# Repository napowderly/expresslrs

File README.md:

# expresslrs

Wooohooo a new package!

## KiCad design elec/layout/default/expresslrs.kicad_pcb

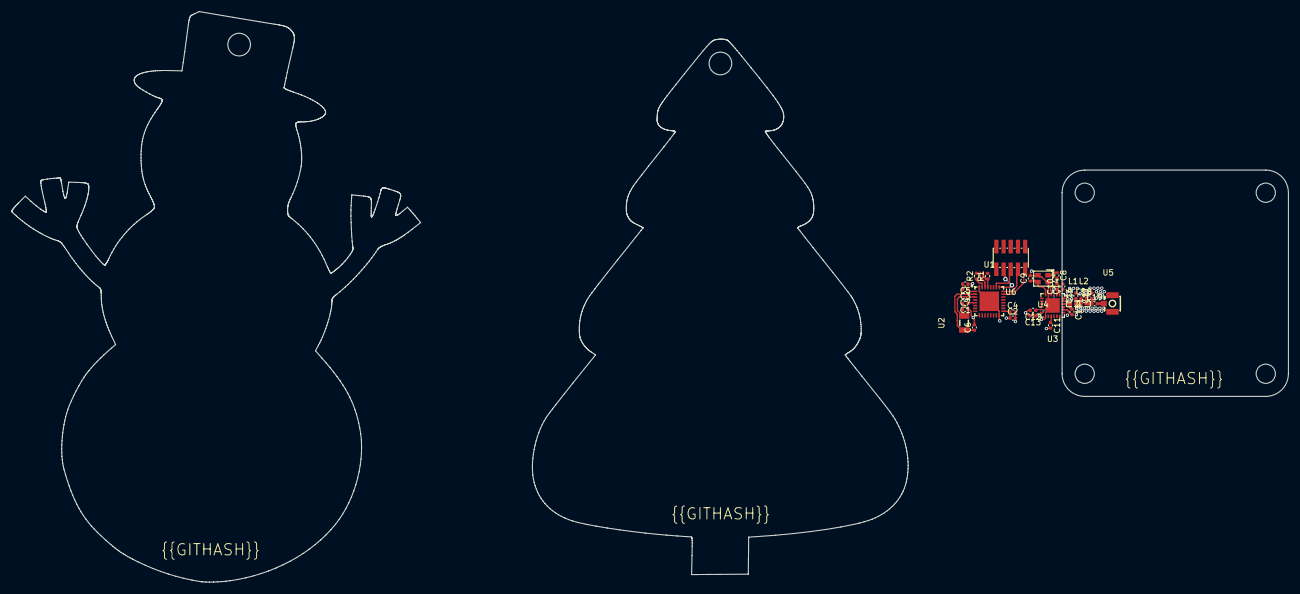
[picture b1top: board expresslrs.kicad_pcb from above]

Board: 2 copper layers, 29 parts (0 on the bottom side), 28 nets.

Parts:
C1: 10V 4.7uF X5R ±20% 0402 Multilayer Ceramic Capaci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; C0402
C2, C4, C11, C12: Multilayer Ceramic Capacitors MLCC - SMD/SMT 100n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; C0402
C3: Multilayer Ceramic Capacitors MLCC - SMD/SMT 1uF 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; C0402
C5, C13, C14: 50V 10nF X7R ±10% 0402 Multilayer Ceramic Capacit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; C0402
C6, C7: 50V 13pF C0G ±2% 0402 Multilayer Ceramic Capacito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; C0402
C8, C9: Multilayer Ceramic Capacitors MLCC - SMD/SMT 10pF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; C0402
C10: 10V 470nF X5R ±10% 0402 Multilayer Ceramic Capaci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; C0402
C15, C18: 50V 1pF C0G 0402 Multilayer Ceramic Capacitors ML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; C0402
C16, C17: Multilayer Ceramic Capacitors MLCC - SMD/SMT 1.2p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; C0402
C19: 50V 100pF C0G ±5% 0402 Multilayer Ceramic Capacit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; C0402
L1, L2: L0402
R1: Chip Resistor - Surface Mount 330Ohms ±5% 1/16W 0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; R0402
R2: Chip Resistor - Surface Mount 10KOhms ±5% 1/16W 0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; R0402
U1: UFQFPN-32_L5.0-W5.0-P0.50-TL-EP3.5
U2: FC-135R_L3.2-W1.5
U3: QFN-24_L4.0-W4.0-P0.50-BL-EP2.6
U4: OSC-SMD_4P-L2.0-W1.6-BL
U5: IPEX-SMD_BWIPX-1-001E
U6: HDR-SMD_10P-P1.27-V-M-R2-C5-LS5.3

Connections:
cs: U1.10, U3.19
gnd: C1.2, C2.2, C3.2, C4.2, C5.2, C6.2, C7.2, C8.2, C9.2, C10.2, C11.2, C12.2, C13.2, C14.2, C15.2, C16.2, C17.2, R2.2, U1.16, U1.32, U1.33, U3.5, U3.13, U3.20, U3.21, U3.23, U3.24, U3.25, U5.2, U5.3, U6.3, U6.5, U6.9
gnd-2: U4.2, U4.4
gnd-3: C19.2, U5.1
io: U1.18, U3.10
io-1: U1.21, U3.7
io-2: U1.27, U3.3
io-3: C15.1, L1.1, U3.22
miso: U1.12, U3.16
mosi: U1.13, U3.17
pc14_osc32_in: C6.1, U1.2, U2.1
pc15_osc32_out: C7.1, U1.3, U2.2
ph3_boot0: R2.1, U1.31
sck: U1.11, U3.18
scl: U1.19, U3.9
sda: U1.20, U3.8
tck: U1.24, U6.4
tdi: U1.25, U6.8
tdo: U1.26, U6.6
tms: U1.23, U6.2
tx: R1.1, U1.29
vcc: C1.1, C2.1, C3.1, C4.1, C5.1, C11.1, C12.1, R1.2, U1.1, U1.5, U1.17, U3.11, U3.15
vcc-2: C14.1, U3.1
vcc-3: C10.1, C13.1, U3.2, U3.12
vcc-5: C16.1, C18.1, L1.2, L2.1
vcc-6: C17.1, C18.2, C19.1, L2.2
xin: C8.1, U4.1
xout: C9.1, U4.3

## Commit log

2024-02-17 Configure project
2024-02-17 intial design
2024-02-17 initial layout
